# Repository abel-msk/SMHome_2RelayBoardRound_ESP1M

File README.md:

# SMHome_UniversalRound_ESP32_C3_Mini
PCB designed board for smart home curtain controll, garage doors or any other equipment with two direction motor
with max power 220v 10A.

Board has ESP-8266 (ESP1M form factor)  two relays and  poweer convertor& 

Main goal of this pcb board is to place  it under wall mounted electric components in socket box, 
but of cource it steel can bee plcad in its own box.

## Haw to use

```
git clone https://github.com/abel-msk/SMHome_2RelayBoardRound_ESP1M
cd SMHome_UniversalRound_ESP32_C3_Mini
```
Next step is to open project file  `SMHome_2RelayBoardRound_ESP1M_v7.kicad_pro`  in KiKad. 

All footprint aggregated in local library `Library.pretty`, shematic symbols in `Library.kicad_sym`. You can add path to this library in project settings.

## 3D view on top of board

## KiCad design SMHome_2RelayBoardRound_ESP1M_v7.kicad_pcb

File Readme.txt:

Финальная версия платы с ESP-01M.   Вертикальная плата  с ESP-8266
Поправлено подключение РЕЛЕ 2 к новому пину.

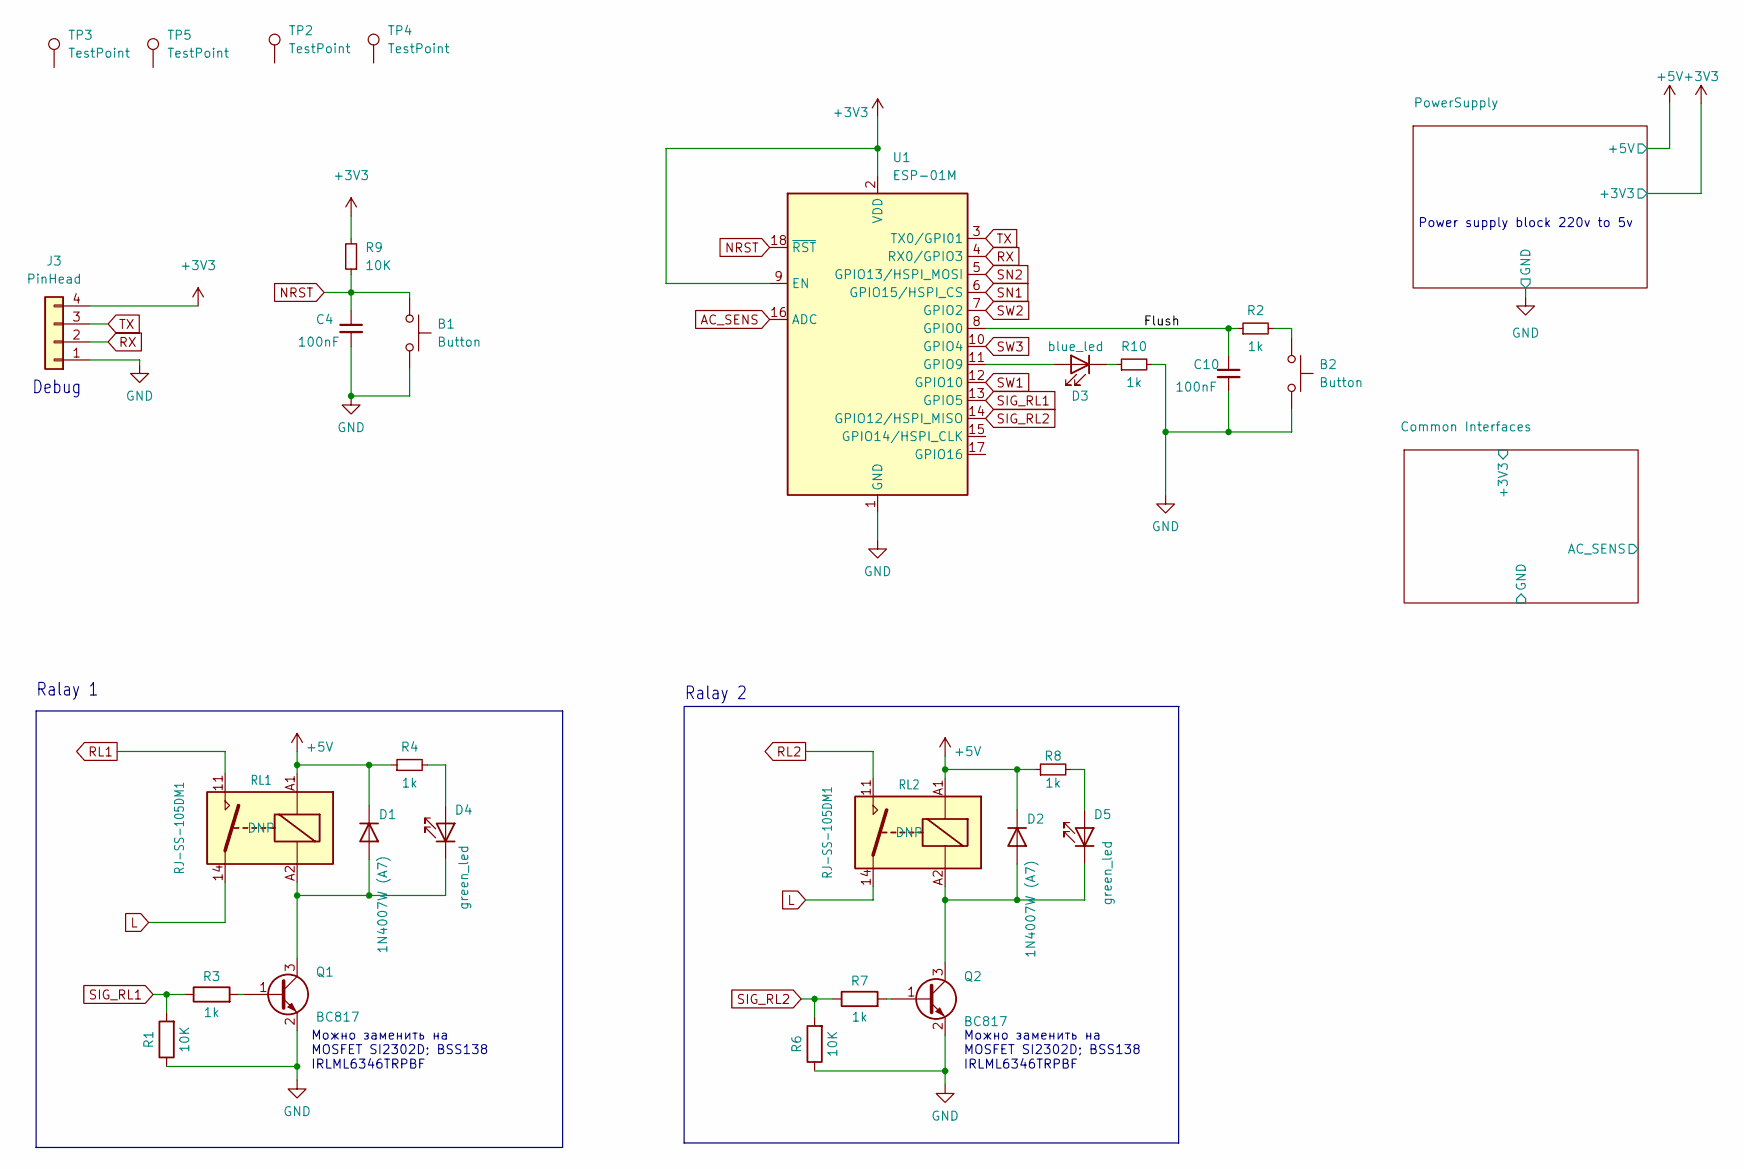
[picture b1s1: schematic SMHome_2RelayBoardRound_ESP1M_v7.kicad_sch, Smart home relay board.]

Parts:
B1, B2: Button; SW_Push_SPST_NO_Alps_SKRK_HandSoldering
C4, C10: 100nF; C_0805_2012Metric
D1, D2: 1N4007W (A7); D_SOD-123F
D3: blue_led; LED_0603_1608Metric_Pad1.05x0.95mm_HandSolder
D4, D5: green_led; LED_0603_1608Metric_Pad1.05x0.95mm_HandSolder
J3: PinHead; PinHeader_1x04_P2.54mm_Vertical
Q1, Q2: BC817; SOT-23
R1, R6, R9: 10K; R_0603_1608Metric_Pad0.98x0.95mm_HandSolder
R2, R3, R4, R7, R8, R10: 1k; R_0603_1608Metric_Pad0.98x0.95mm_HandSolder
RL1, RL2: RJ-SS-105DM1
TP2, TP3, TP4, TP5: TestPoint; TestPoint_THTPad_D2.0mm_Drill1.0mm
U1: ESP-01M

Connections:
+3V3: J3.4, R9.2, U1.2 (VDD), U1.9 (EN); also elsewhere on the board
+5V: D1.1 (K), D2.1 (K), R4.1, R8.1, RL1.A1, RL2.A1; also elsewhere on the board
/Flush: C10.1, R2.1, U1.8 (GPIO0)
AC_SENS: U1.16 (ADC); also elsewhere on the board
GND: B1.2, B2.2, C4.2, C10.2, J3.1, Q1.2 (E), Q2.2 (E), R1.1, R6.1, R10.2, U1.1 (GND); also elsewhere on the board
L: RL1.14, RL2.14; also elsewhere on the board
NRST: B1.1, C4.1, R9.1, U1.18 (~RST)
unnamed: B2.1, R2.2
unnamed: D1.2 (A), D4.1 (K), Q1.3 (C), RL1.A2
unnamed: D2.2 (A), D5.1 (K), Q2.3 (C), RL2.A2
unnamed: D3.2 (A), U1.11 (GPIO9)
unnamed: D3.1 (K), R10.1
unnamed: D4.2 (A), R4.2
unnamed: D5.2 (A), R8.2
unnamed: Q1.1 (B), R3.2
unnamed: Q2.1 (B), R7.2
RL1: RL1.11; also elsewhere on the board
RL2: RL2.11; also elsewhere on the board
RX: J3.2, U1.4 (RX0/GPIO3)
SIG_RL1: R1.2, R3.1, U1.13 (GPIO5)
SIG_RL2: R6.2, R7.1, U1.14 (GPIO12/HSPI_MISO)
SN1: U1.6 (GPIO15/HSPI_CS); also elsewhere on the board
SN2: U1.5 (GPIO13/HSPI_MOSI); also elsewhere on the board
SW1: U1.12 (GPIO10); also elsewhere on the board
SW2: U1.7 (GPIO2); also elsewhere on the board
SW3: U1.10 (GPIO4); also elsewhere on the board
TX: J3.3, U1.3 (TX0/GPI01)

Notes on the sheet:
Power supply block 220v to 5v
Можно заменить на MOSFET SI2302D; BSS138 IRLML6346TRPBF
Debug
Ralay 2
Ralay 1

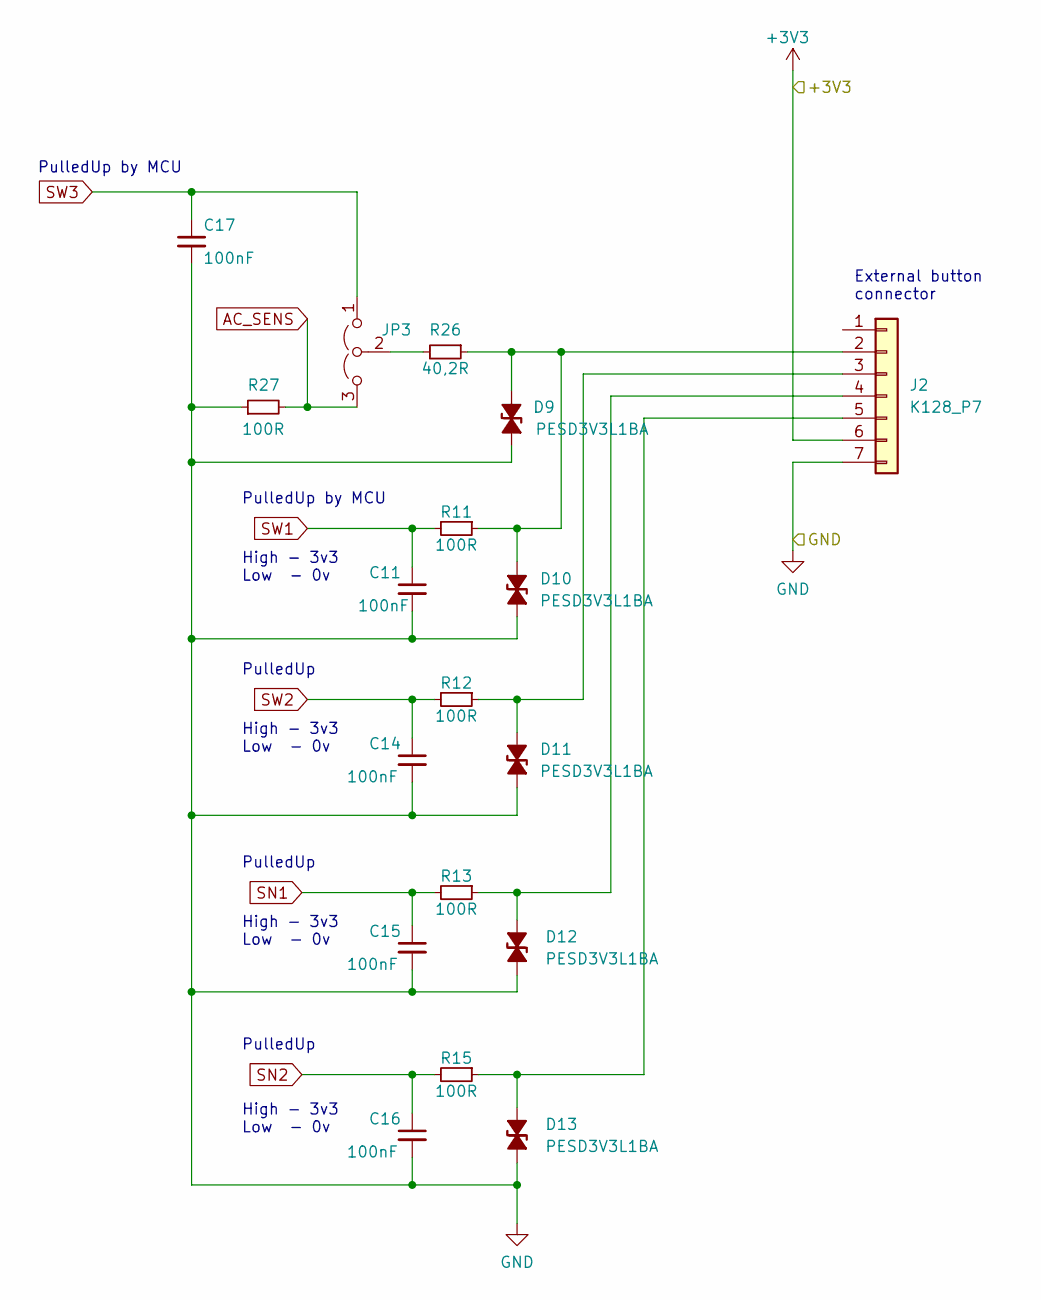
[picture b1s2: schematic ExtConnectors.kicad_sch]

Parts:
C11, C14, C15, C16, C17: 100nF; C_0805_2012Metric
D9, D10, D11, D12, D13: PESD3V3L1BA; D_SOD-323_HandSoldering
J2: K128_P7; Phoenix Contact_MPT-0,5_7_2,54_P7
JP3: jmp3; SolderJumper-3_P1.3mm_Open_RoundedPad1.0x1.5mm_NumberLabels
R11, R12, R13, R15, R27: 100R; R_0603_1608Metric_Pad0.98x0.95mm_HandSolder
R26: 40,2R; R_0603_1608Metric_Pad0.98x0.95mm_HandSolder

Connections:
+3V3: J2.6; also elsewhere on the board
AC_SENS: JP3.3 (B), R27.2; also elsewhere on the board
GND: C11.2, C14.2, C15.2, C16.2, C17.2, D9.1 (K), D10.1 (K), D11.2 (A), D12.2 (A), D13.2 (A), J2.7, R27.1; also elsewhere on the board
unnamed: D9.2 (A), D10.2 (A), J2.2, R11.1, R26.1
unnamed: D11.1 (K), J2.3, R12.1
unnamed: D12.1 (K), J2.4, R13.1
unnamed: D13.1 (K), J2.5, R15.1
unnamed: JP3.2 (C), R26.2
SN1: C15.1, R13.2; also elsewhere on the board
SN2: C16.1, R15.2; also elsewhere on the board
SW1: C11.1, R11.2; also elsewhere on the board
SW2: C14.1, R12.2; also elsewhere on the board
SW3: C17.1, JP3.1 (A); also elsewhere on the board

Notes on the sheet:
External button connector
PulledUp
PulledUp by MCU
High - 3v3 Low - 0v

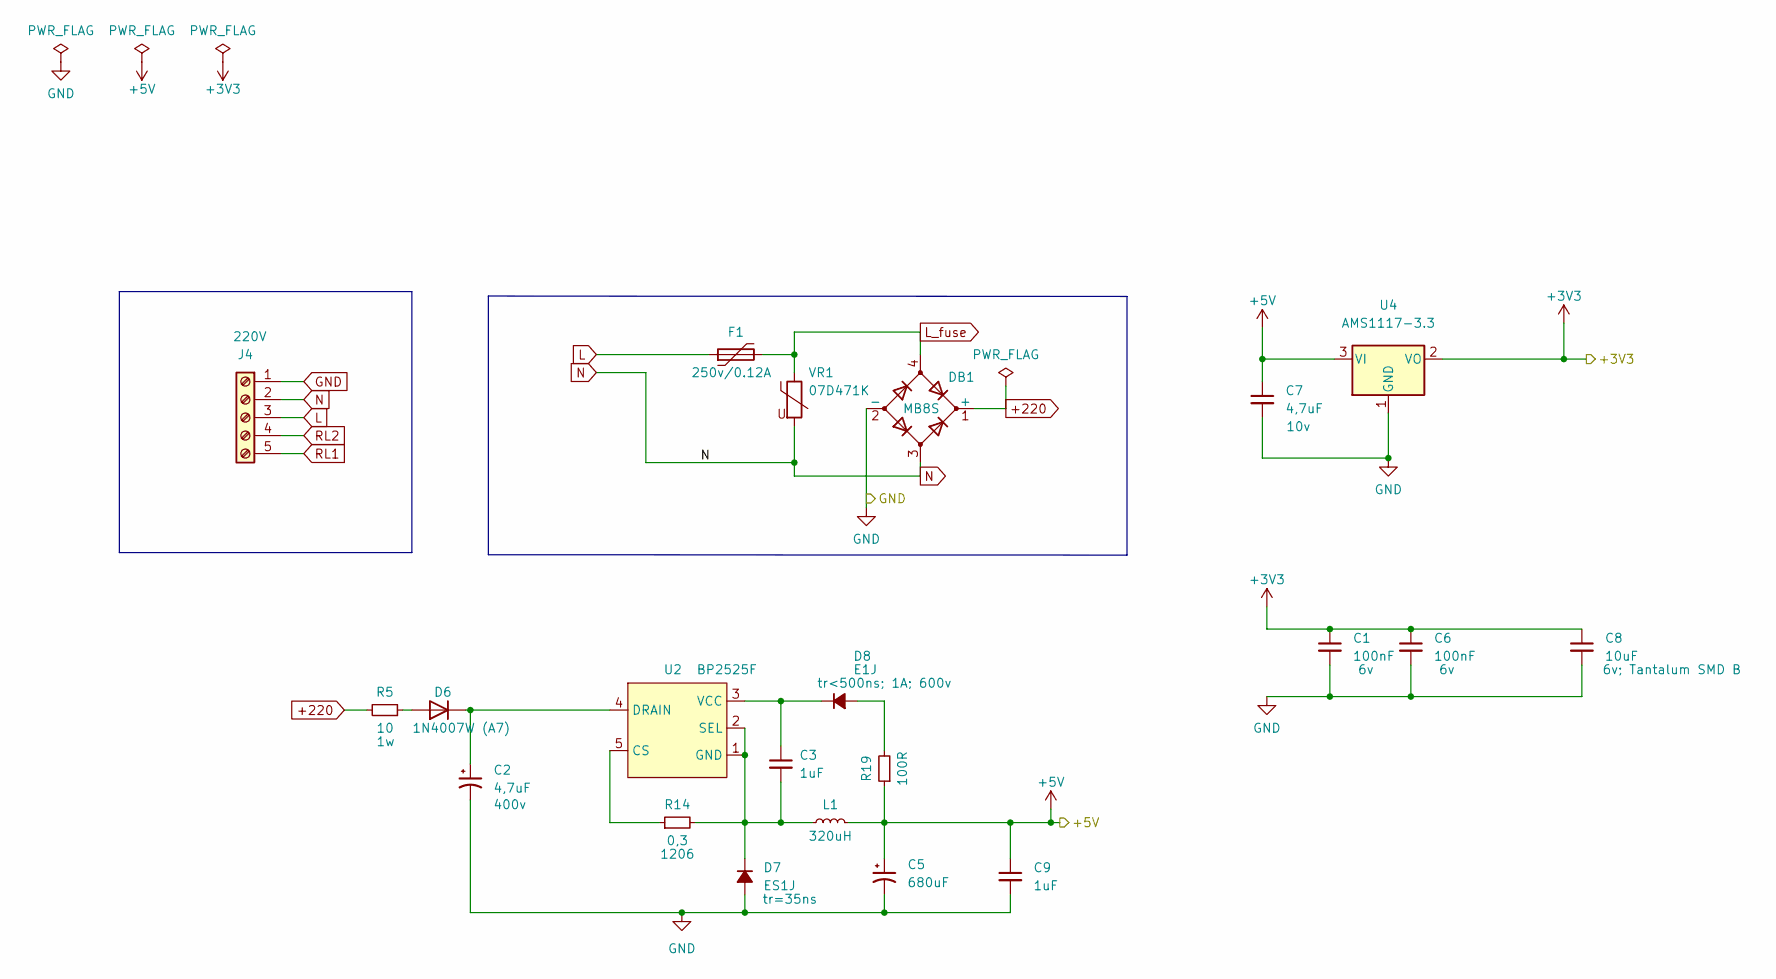
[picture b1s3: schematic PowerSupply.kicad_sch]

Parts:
C1, C6: 100nF; C_0805_2012Metric
C2: 4,7uF; CP_Radial_D8.0mm_P3.80mm
C3, C9: 1uF; C_0805_2012Metric_Pad1.18x1.45mm_HandSolder
C5: 680uF; CP_Radial_D6.3mm_P2.50mm
C7: 4,7uF; C_0805_2012Metric_Pad1.18x1.45mm_HandSolder
C8: 10uF; CP_EIA-3528-21_Kemet-B
D6: 1N4007W (A7); D_SOD-123F
D7: ES1J; D_SMA
D8: E1J; D_SOD-123F
DB1: MB8S; MBS
F1: 250v/0.12A; RF145_D6.5mm_W4mm
J4: 220V; DG301-5.0-05P
L1: 320uH; L_Radial_D10.0mm_P5.00mm_Fastron_07P
R5: 10; R_Axial_DIN0414_L11.9mm_D4.5mm_P5.08mm_Vertical
R14: 0,3; R_1206_3216Metric_Pad1.30x1.75mm_HandSolder
R19: 100R; R_0603_1608Metric_Pad0.98x0.95mm_HandSolder
U2: BP2525F; SOT33-5
U4: AMS1117-3.3; SOT-223-3_TabPin1
VR1: 07D471K; RV_Disc_D9mm_W3.3mm_P5mm

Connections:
+3V3: C1.1, C6.1, C8.1, U4.2 (VO); also elsewhere on the board
+5V: C5.1, C7.1, C9.1, L1.2, R19.1, U4.3 (VI); also elsewhere on the board
+220: DB1.1 (+), R5.2
GND: C1.2, C2.2, C5.2, C6.2, C7.2, C8.2, C9.2, D7.2 (A), DB1.2 (-), J4.1, U4.1 (GND); also elsewhere on the board
L: F1.1, J4.3; also elsewhere on the board
L_fuse: DB1.4, F1.2, VR1.1
N: DB1.3, J4.2, VR1.2
unnamed: D6.2 (A), R5.1
unnamed: C2.1, D6.1 (K), U2.4 (DRAIN)
unnamed: C3.2, D7.1 (K), L1.1, R14.2, U2.1 (GND), U2.2 (SEL)
unnamed: D8.2 (A), R19.2
unnamed: C3.1, D8.1 (K), U2.3 (VCC)
unnamed: R14.1, U2.5 (CS)
RL1: J4.5; also elsewhere on the board
RL2: J4.4; also elsewhere on the board

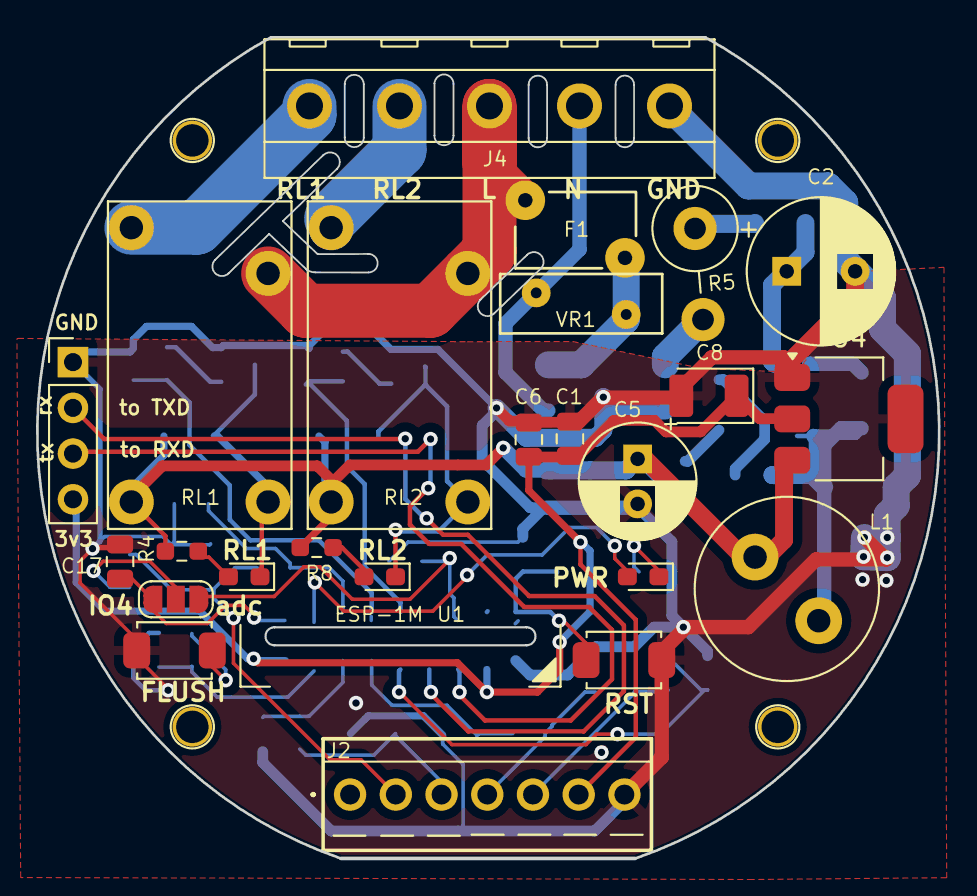
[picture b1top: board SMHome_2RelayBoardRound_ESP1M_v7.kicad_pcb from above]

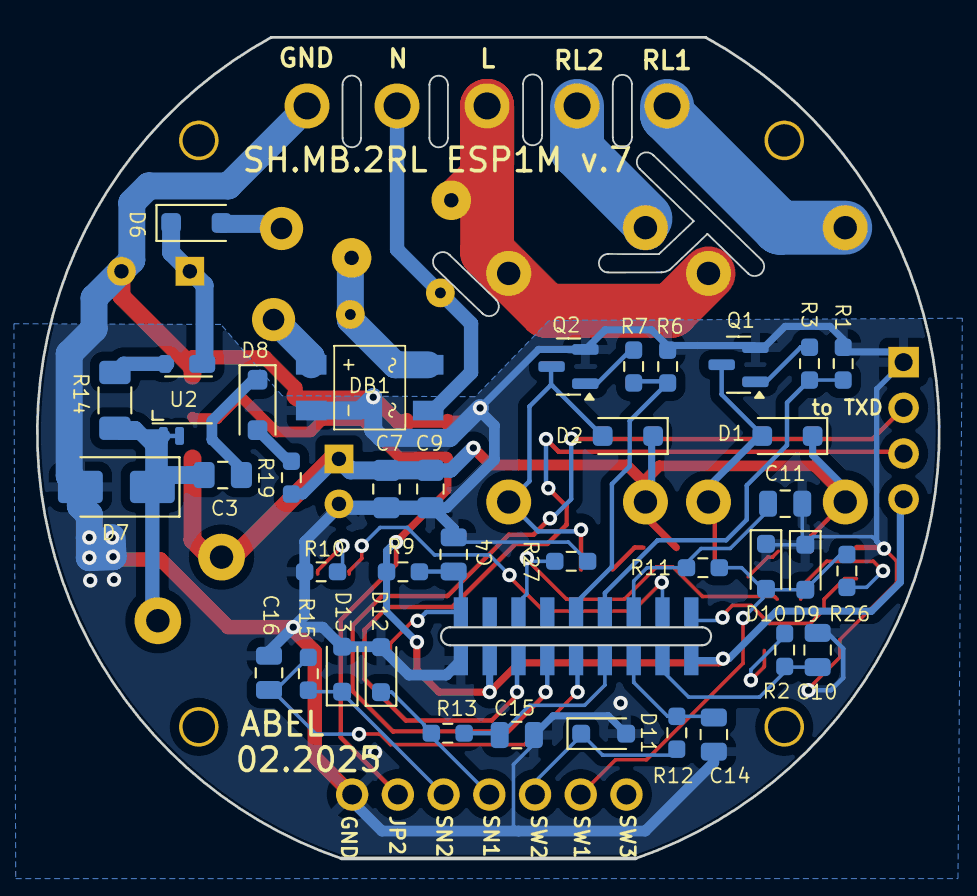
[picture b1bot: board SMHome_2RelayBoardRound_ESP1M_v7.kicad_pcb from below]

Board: 2 copper layers, 50.1 x 45.6 mm, 67 parts (38 on the bottom side), 41 nets.

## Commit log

2025-02-24 add gitignore
2025-11-26 Migrated to KiKad9
